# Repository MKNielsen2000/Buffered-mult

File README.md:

# Buffered-mult
A simple, compact 2 x 1:3 / 1 x 1:6 buffered multiple for eurorack utilising high quality OPA4171/OPA2171 opamps for suave sound performance and 1206 components to make it easy for anyone to solder.

This circuit is inspired by [Mutable Instruments LINKS.](http://mutable-instruments.net/modules/links)

###It works like this:

#####1:6 mult
Plug a cable into the IN1 jack to get a signal distributed in a 1:out mult.

#####2 x 1:3 mult
Plug one cable into IN1 and another into IN2/OUT4 and boom, the signal at each of the two inputs is then distributed in 1:3 mults.

Status:

95%
███████▒

Layout done, need to test and verify.

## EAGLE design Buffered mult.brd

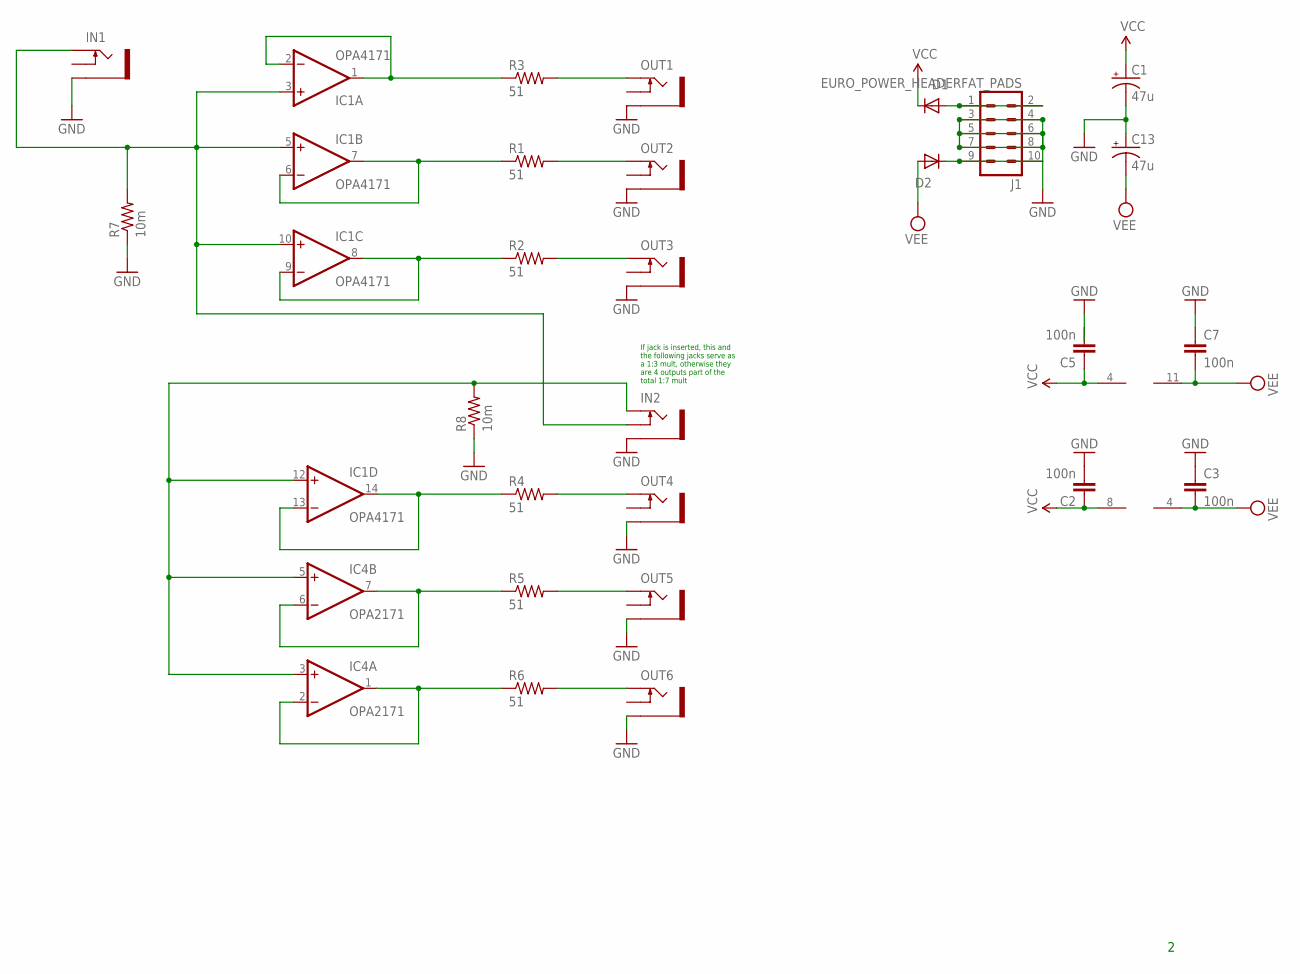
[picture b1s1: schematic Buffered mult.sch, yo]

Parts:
C1, C13: 47u; PANASONIC_D
C2, C3, C5, C7: 100n; 1206
D1, D2: 1N5819HW; SOD123
IC1: OPA4171; TSSOP14
IC4: OPA2171; SO08
IN1, IN2: PJ302M
J1: EURO_POWER_HEADERFAT_PADS; EURO_PWR_HEADER_FAT
OUT1, OUT2, OUT3, OUT4, OUT5, OUT6: PJ302M
R1, R2, R3, R4, R5, R6: 51; 1206
R7, R8: 10m; 1206

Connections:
GND: C1.-, C2.2, C3.1, C5.2, C7.1, C13.+, IN1.GND (SLEEVE), IN2.GND (SLEEVE), J1.3, J1.4, J1.5, J1.6, J1.7, J1.8, OUT1.GND (SLEEVE), OUT2.GND (SLEEVE), OUT3.GND (SLEEVE), OUT4.GND (SLEEVE), OUT5.GND (SLEEVE), OUT6.GND (SLEEVE), R7.1, R8.1
unnamed: OUT6.TIP, R6.2
unnamed: IC1.1 (OUT), IC1.2 (-IN), R3.1
unnamed: OUT5.TIP, R5.2
unnamed: OUT4.TIP, R4.2
unnamed: IC1.3 (+IN), IC1.5 (+IN), IC1.10 (+IN), IN1.TIP, IN2.SW (SWITCH), R7.2
unnamed: IC1.8 (OUT), IC1.9 (-IN), R2.1
unnamed: OUT2.TIP, R1.2
unnamed: OUT3.TIP, R2.2
unnamed: OUT1.TIP, R3.2
unnamed: IC1.6 (-IN), IC1.7 (OUT), R1.1
unnamed: IC4.1 (OUT), IC4.2 (-IN), R6.1
unnamed: IC4.6 (-IN), IC4.7 (OUT), R5.1
unnamed: D2.C, J1.9, J1.10
unnamed: D1.A, J1.1, J1.2
unnamed: IC1.13 (-IN), IC1.14 (OUT), R4.1
unnamed: IC1.12 (+IN), IC4.3 (+IN), IC4.5 (+IN), IN2.TIP, R8.2
VCC: C1.+, C2.1, C5.1, D1.C, IC1.4 (V+), IC4.8 (V+)
VEE: C3.2, C7.2, C13.-, D2.A, IC1.11 (V-), IC4.4 (V-)

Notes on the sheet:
If jack is inserted, this and the following jacks serve as a 1:3 mult, otherwise they are 4 outputs part of the total 1:7 mult

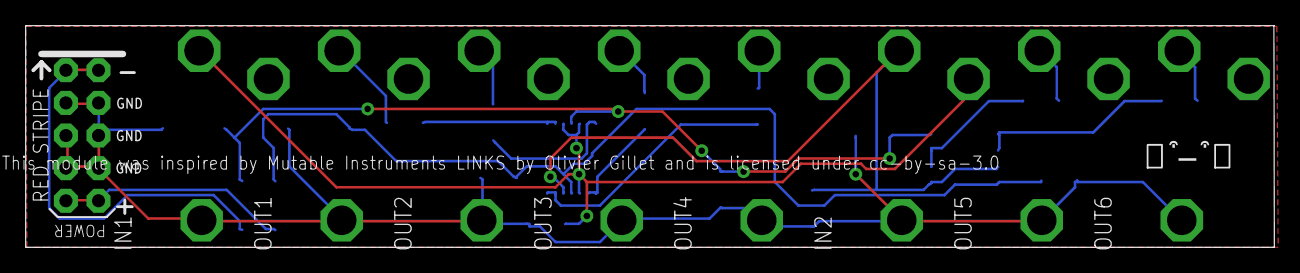
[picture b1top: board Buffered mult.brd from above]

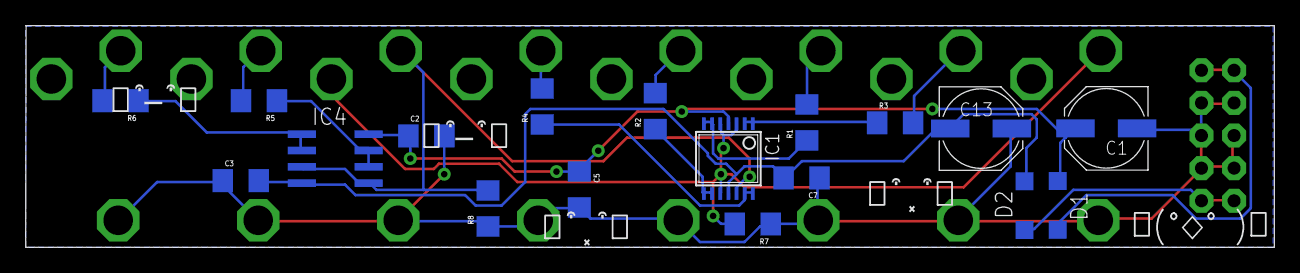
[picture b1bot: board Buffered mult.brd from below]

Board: 2 copper layers, 97.2 x 17.2 mm, 27 parts (18 on the bottom side), 19 nets.

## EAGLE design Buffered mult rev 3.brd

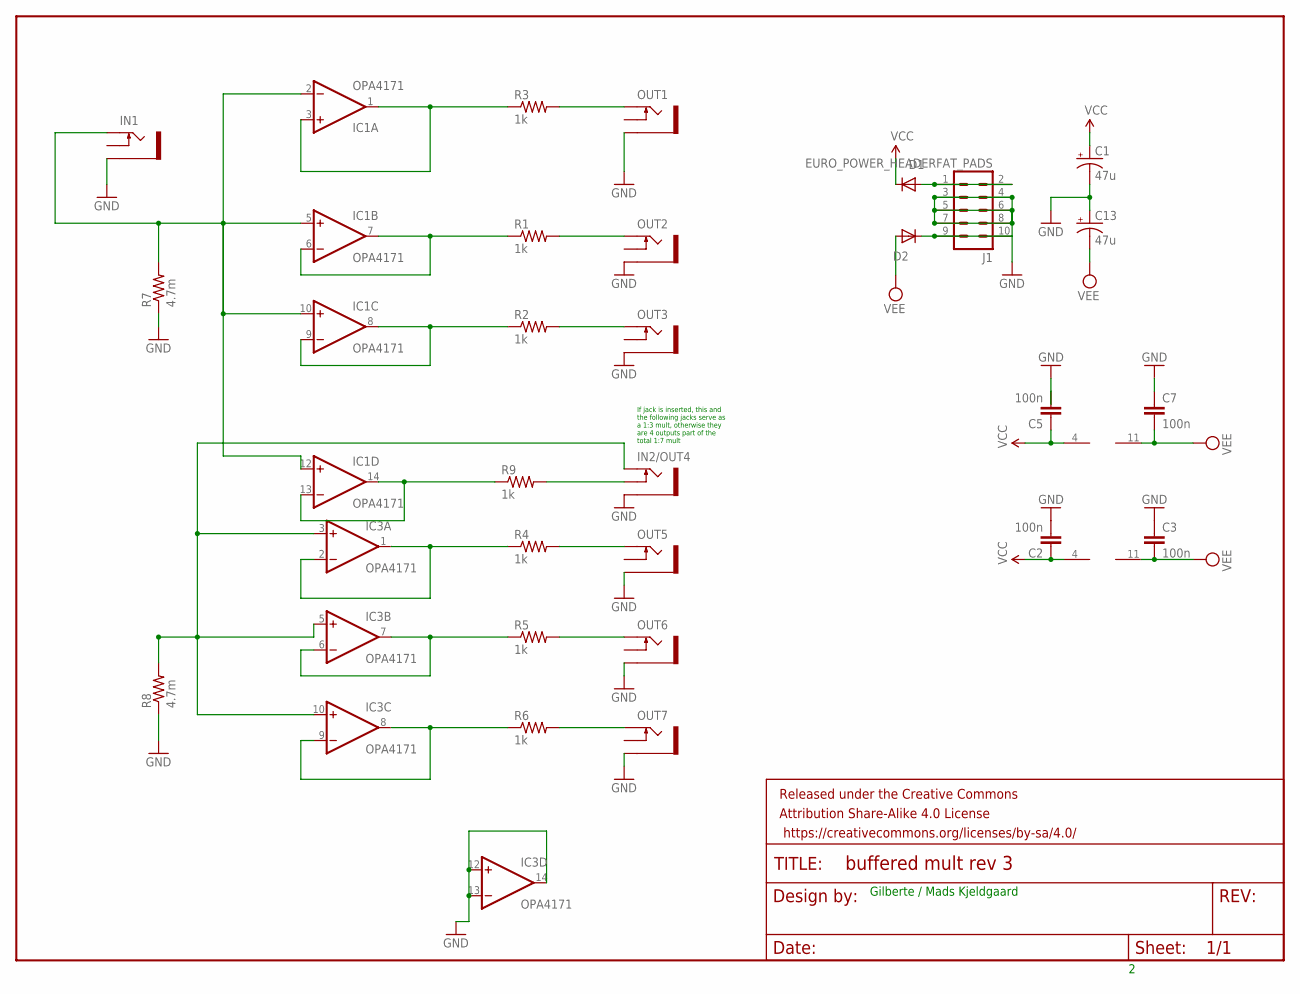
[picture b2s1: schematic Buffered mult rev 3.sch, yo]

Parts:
C1, C13: 47u; PANASONIC_D
C2, C3, C5, C7: 100n; 1206
D1, D2: 1N5819HW; SOD123
FRAME1: FRAME-LETTER; CREATIVE_COMMONS
IC1, IC3: OPA4171; TSSOP14
IN1, IN2/OUT4: PJ302M
J1: EURO_POWER_HEADERFAT_PADS; EURO_PWR_HEADER_FAT
OUT1, OUT2, OUT3, OUT5, OUT6, OUT7: PJ302M
R1, R2, R3, R4, R5, R6, R9: 1k; 1206
R7, R8: 4.7m; 1206

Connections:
GND: C1.-, C2.2, C3.1, C5.2, C7.1, C13.+, IC3.12 (+IN), IC3.13 (-IN), IC3.14 (OUT), IN1.GND (SLEEVE), IN2/OUT4.GND (SLEEVE), J1.3, J1.4, J1.5, J1.6, J1.7, J1.8, OUT1.GND (SLEEVE), OUT2.GND (SLEEVE), OUT3.GND (SLEEVE), OUT5.GND (SLEEVE), OUT6.GND (SLEEVE), OUT7.GND (SLEEVE), R7.1, R8.1
unnamed: OUT7.TIP, R6.2
unnamed: IC1.1 (OUT), IC1.3 (+IN), R3.1
unnamed: OUT6.TIP, R5.2
unnamed: OUT5.TIP, R4.2
unnamed: IC1.2 (-IN), IC1.5 (+IN), IC1.10 (+IN), IC1.12 (+IN), IN1.TIP, R7.2
unnamed: IC1.8 (OUT), IC1.9 (-IN), R2.1
unnamed: OUT2.TIP, R1.2
unnamed: OUT3.TIP, R2.2
unnamed: OUT1.TIP, R3.2
unnamed: IC1.6 (-IN), IC1.7 (OUT), R1.1
unnamed: IC3.8 (OUT), IC3.9 (-IN), R6.1
unnamed: IC3.6 (-IN), IC3.7 (OUT), R5.1
unnamed: D2.C, J1.9, J1.10
unnamed: D1.A, J1.1, J1.2
unnamed: IC1.13 (-IN), IC1.14 (OUT), R9.1
unnamed: IC3.1 (OUT), IC3.2 (-IN), R4.1
unnamed: IN2/OUT4.SW (SWITCH), R9.2
unnamed: IC3.3 (+IN), IC3.5 (+IN), IC3.10 (+IN), IN2/OUT4.TIP, R8.2
VCC: C1.+, C2.1, C5.1, D1.C, IC1.4 (V+), IC3.4 (V+)
VEE: C3.2, C7.2, C13.-, D2.A, IC1.11 (V-), IC3.11 (V-)

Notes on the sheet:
Gilberte / Mads Kjeldgaard
If jack is inserted, this and the following jacks serve as a 1:3 mult, otherwise they are 4 outputs part of the total 1:7 mult

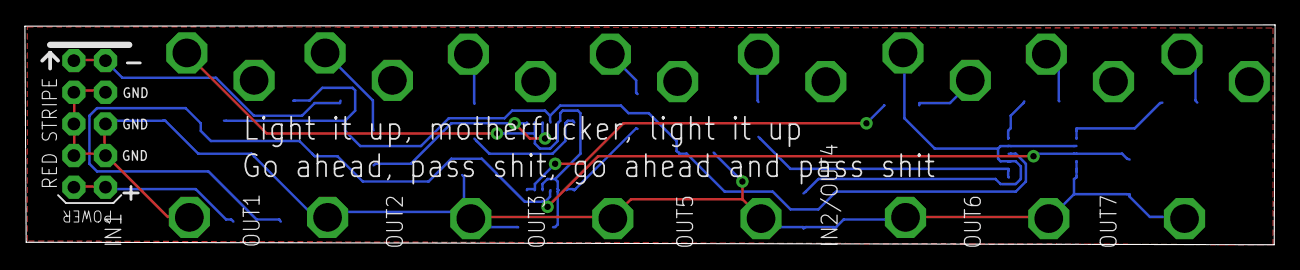
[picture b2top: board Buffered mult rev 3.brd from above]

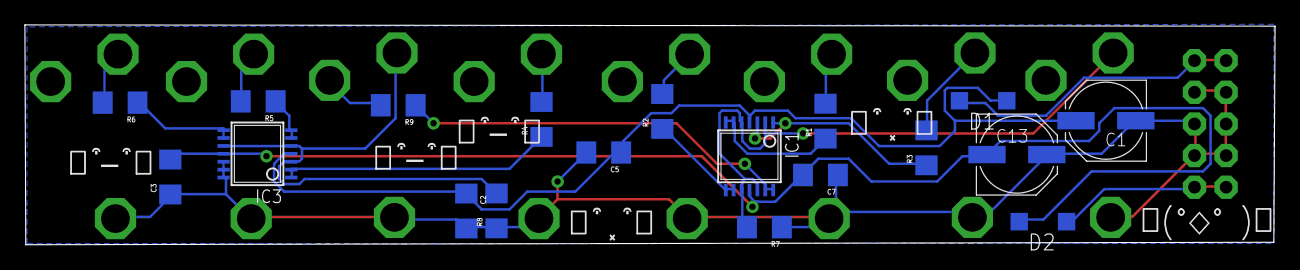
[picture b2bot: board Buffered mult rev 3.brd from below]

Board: 2 copper layers, 100.4 x 17.6 mm, 29 parts (19 on the bottom side), 21 nets.

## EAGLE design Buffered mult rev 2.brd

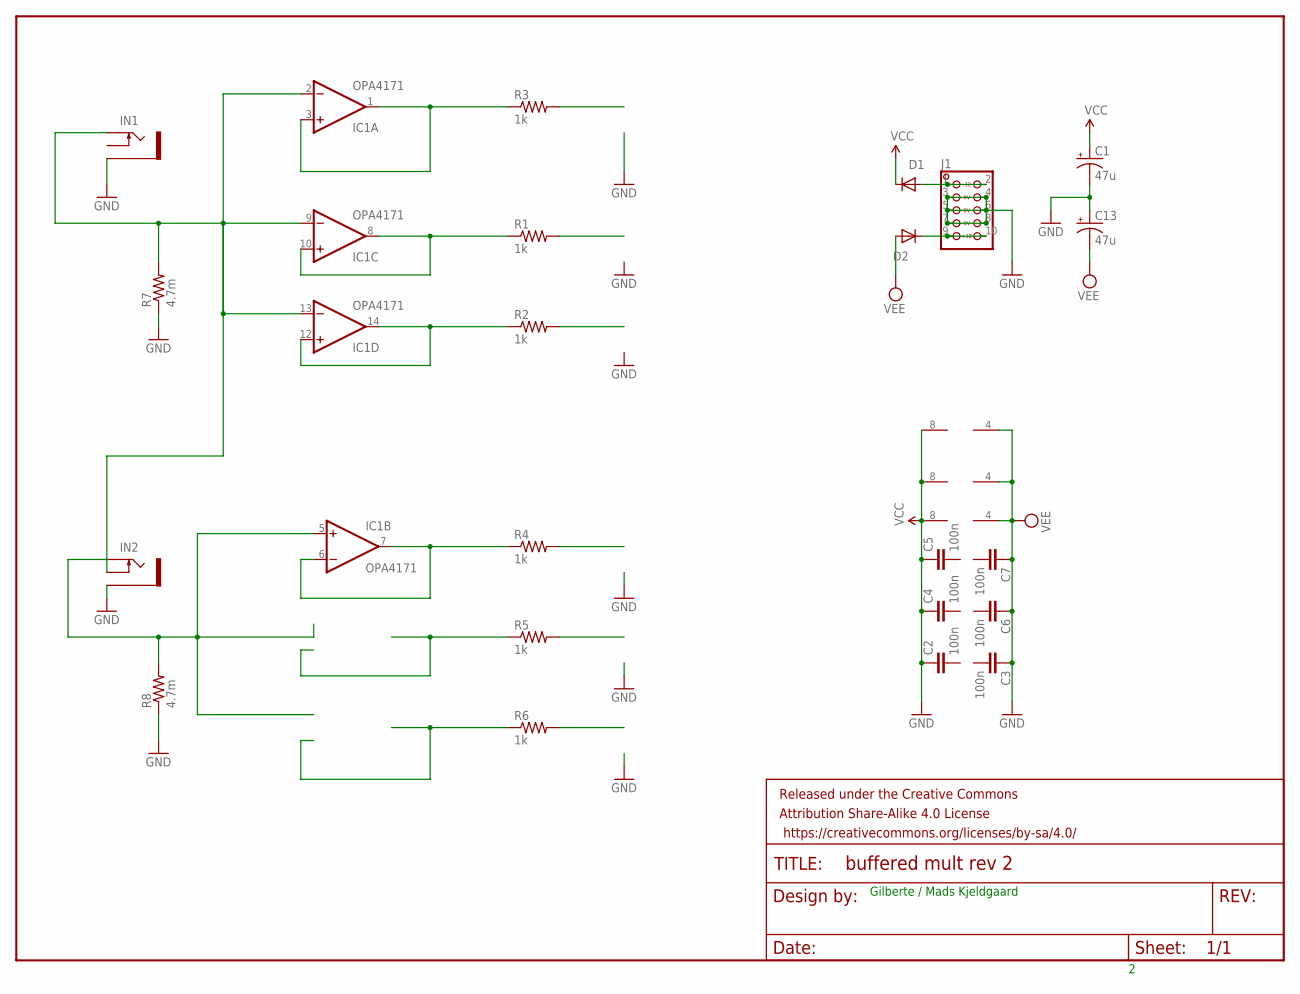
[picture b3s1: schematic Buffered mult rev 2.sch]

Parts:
C1, C13: 47u; PANASONIC_D
C2, C3, C4, C5, C6, C7: 100n; 1206
D1, D2: 1N5819HW; SOD123
FRAME1: FRAME-LETTER; CREATIVE_COMMONS
IC1: OPA4171; TSSOP14
IN1, IN2: THONKICONNOLD; THONKICONN
J1: EUROPWR_2X05-SMD; 2X05_EUROPWR_SMD
R1, R2, R3, R4, R5, R6: 1k; 1206
R7, R8: 4.7m; 1206
U1, U2, U3: TL072_SMD; SO08

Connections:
GND: C1.-, C2.1, C3.1, C4.1, C5.1, C6.1, C7.1, C13.+, IN1.P$1_SLEEVE (SLEEVE), IN2.P$1_SLEEVE (SLEEVE), J1.3, J1.4, J1.5, J1.6, J1.7, J1.8, R7.1, R8.1, U1.4 (V-), U1.8 (V+), U2.4 (V-), U2.8 (V+), U3.4 (V-), U3.8 (V+)
unnamed: IC1.1 (OUT), IC1.3 (+IN), R3.1, U1.1 (OUT), U1.2 (-IN)
unnamed: IC1.2 (-IN), IC1.9 (-IN), IC1.13 (-IN), IN1.P$3_TIP (TIP), IN2.P$2_SWITCH (SWITCH), R7.2, U1.3 (+IN), U1.5 (+IN), U2.3 (+IN)
unnamed: IC1.12 (+IN), IC1.14 (OUT), R2.1, U2.1 (OUT), U2.2 (-IN)
unnamed: IC1.8 (OUT), IC1.10 (+IN), R1.1, U1.6 (-IN), U1.7 (OUT)
unnamed: IC1.5 (+IN), IN2.P$3_TIP (TIP), R8.2, U2.5 (+IN), U3.3 (+IN), U3.5 (+IN)
unnamed: R6.1, U3.6 (-IN), U3.7 (OUT)
unnamed: R5.1, U3.1 (OUT), U3.2 (-IN)
unnamed: D2.C, J1.9, J1.10
unnamed: D1.A, J1.1, J1.2
unnamed: IC1.6 (-IN), IC1.7 (OUT), R4.1, U2.6 (-IN), U2.7 (OUT)
VCC: C1.+, D1.C
VEE: C13.-, D2.A

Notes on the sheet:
Gilberte / Mads Kjeldgaard

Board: 2 copper layers, 25 parts (16 on the bottom side), 13 nets, no tracks yet.

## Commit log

2016-05-22 minor adjustments to schem
2016-05-22 Rev 2 made. Changed opamps to tl072 so they fit between the jack pins
2016-05-25 Opaxx71 version laid out, optimized pj302m jacks and did a first draft of pcb layout
2016-05-25 minor changes
2016-05-25 Layout done.
2016-05-25 Finalized design, generated Gerbers.
2016-05-25 ready update
2016-05-25 readme update
2016-05-25 fixed error in schematic
2016-05-25 board update
2016-05-25 new revision: Changed IC2 to opa2171, fixed switch jack
2016-05-25 small touchups
2016-05-25 last donut of the night

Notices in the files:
Buffered mult.brd:
This module was inspired by Mutable Instruments LINKS by Olivier Gillet and is licensed under cc-by-sa-3.0
parts and their libraries:
SparkFun-Capacitors: Licensing: Creative Commons ShareAlike 4.0 International - https://creativecommons.org/licenses/by-sa/4.0
SparkFun-Aesthetics: Released under the Creative Commons Attribution Share-Alike 4.0 License
SparkFun-Aesthetics: https://creativecommons.org/licenses/by-sa/4.0
